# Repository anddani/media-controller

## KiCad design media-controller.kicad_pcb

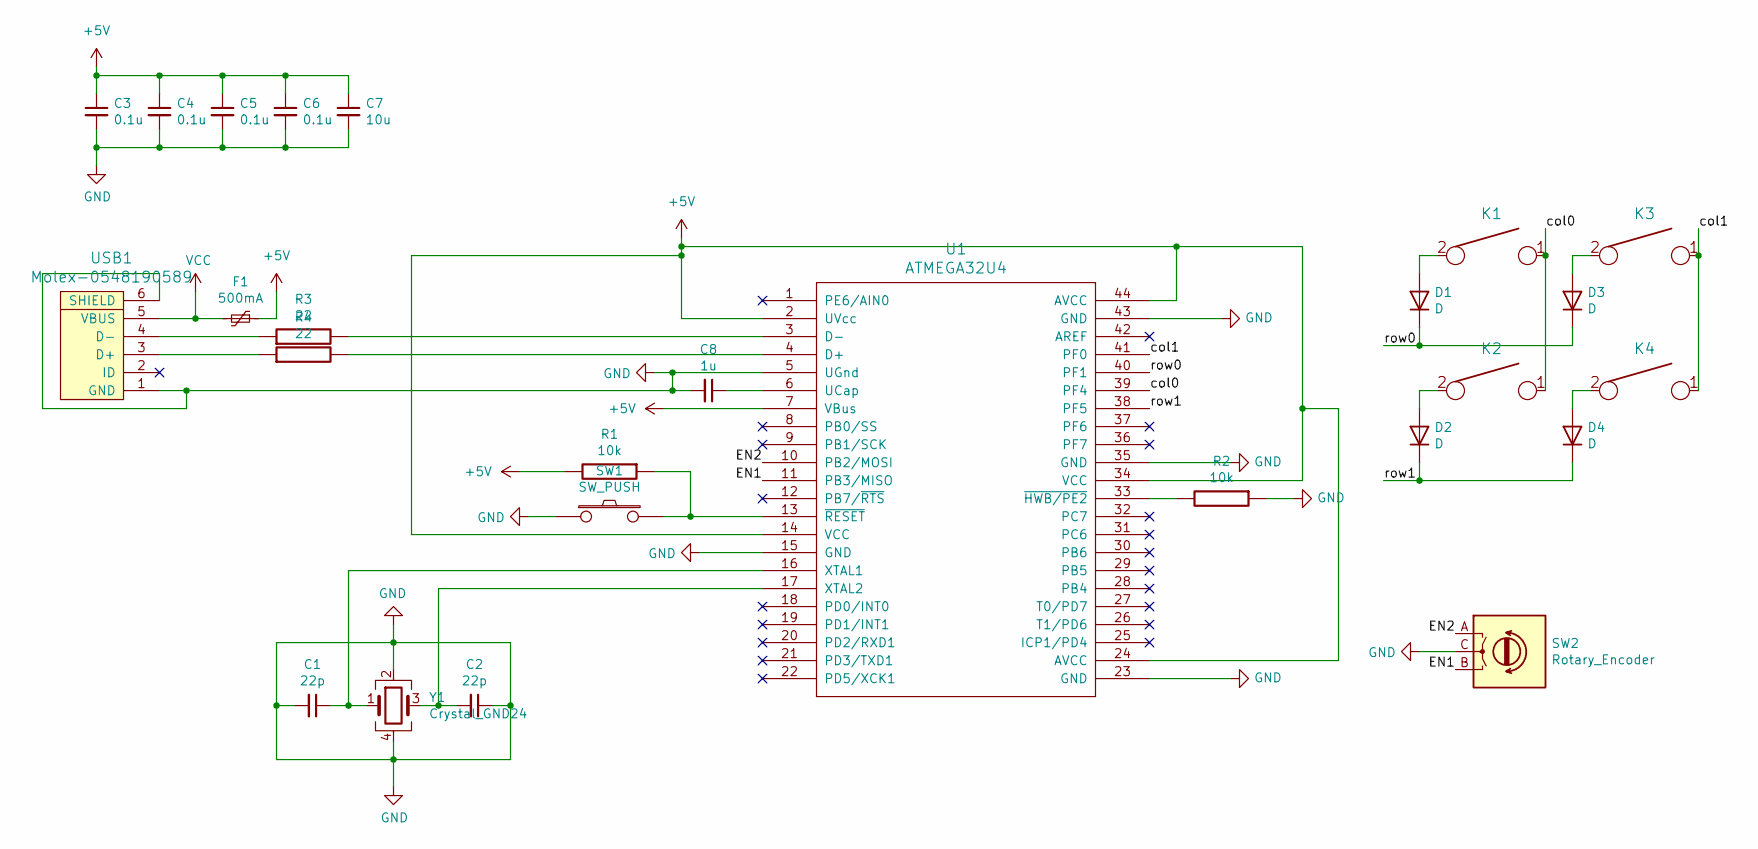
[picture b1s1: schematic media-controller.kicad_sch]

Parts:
C1, C2: 22p; C_0805_2012Metric
C3, C4, C5, C6: 0.1u; C_0805_2012Metric
C7: 10u; C_0805_2012Metric
C8: 1u; C_0805_2012Metric
D1, D2, D3, D4: D; D_SOD-123
F1: 500mA; Fuse_1206_3216Metric
K1, K2, K3, K4: KEYSW; MXOnly-1U-NoLED
R1, R2: 10k; R_0805_2012Metric
R3, R4: 22; R_0805_2012Metric
SW1: SW_PUSH; SKQG-1155865
SW2: Rotary_Encoder; RotaryEncoder_Alps_EC12E-Switch_Vertical_H20mm
U1: ATMEGA32U4; TQFP-44_10x10mm_P0.8mm
USB1: Molex-0548190589
Y1: Crystal_GND24; Crystal_SMD_3225-4Pin_3.2x2.5mm

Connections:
+5V: C3.1, C4.1, C5.1, C6.1, C7.1, F1.1, R1.2, U1.2 (UVcc), U1.7 (VBus), U1.14 (VCC), U1.24 (AVCC), U1.34 (VCC), U1.44 (AVCC)
/EN1: SW2.B, U1.11 (PB3/MISO)
/EN2: SW2.A, U1.10 (PB2/MOSI)
/col0: K1.1, K2.1, U1.39 (PF4)
/col1: K3.1, K4.1, U1.41 (PF0)
/row0: D1.1 (K), D3.1 (K), U1.40 (PF1)
/row1: D2.1 (K), D4.1 (K), U1.38 (PF5)
GND: C1.2, C2.1, C3.2, C4.2, C5.2, C6.2, C7.2, C8.2, R2.1, SW1.1, SW2.C, U1.5 (UGnd), U1.15 (GND), U1.23 (GND), U1.35 (GND), U1.43 (GND), USB1.1 (GND), USB1.6 (SHIELD), Y1.2, Y1.4
unnamed: C1.1, U1.16 (XTAL1), Y1.1
unnamed: C2.2, U1.17 (XTAL2), Y1.3
unnamed: C8.1, U1.6 (UCap)
unnamed: D1.2 (A), K1.2
unnamed: D2.2 (A), K2.2
unnamed: D3.2 (A), K3.2
unnamed: D4.2 (A), K4.2
unnamed: R1.1, SW1.2, U1.13 (~RESET)
unnamed: R2.2, U1.33 (~HWB/PE2)
unnamed: R3.1, USB1.4 (D-)
unnamed: R3.2, U1.3 (D-)
unnamed: R4.1, USB1.3 (D+)
unnamed: R4.2, U1.4 (D+)
VCC: F1.2, USB1.5 (VBUS)

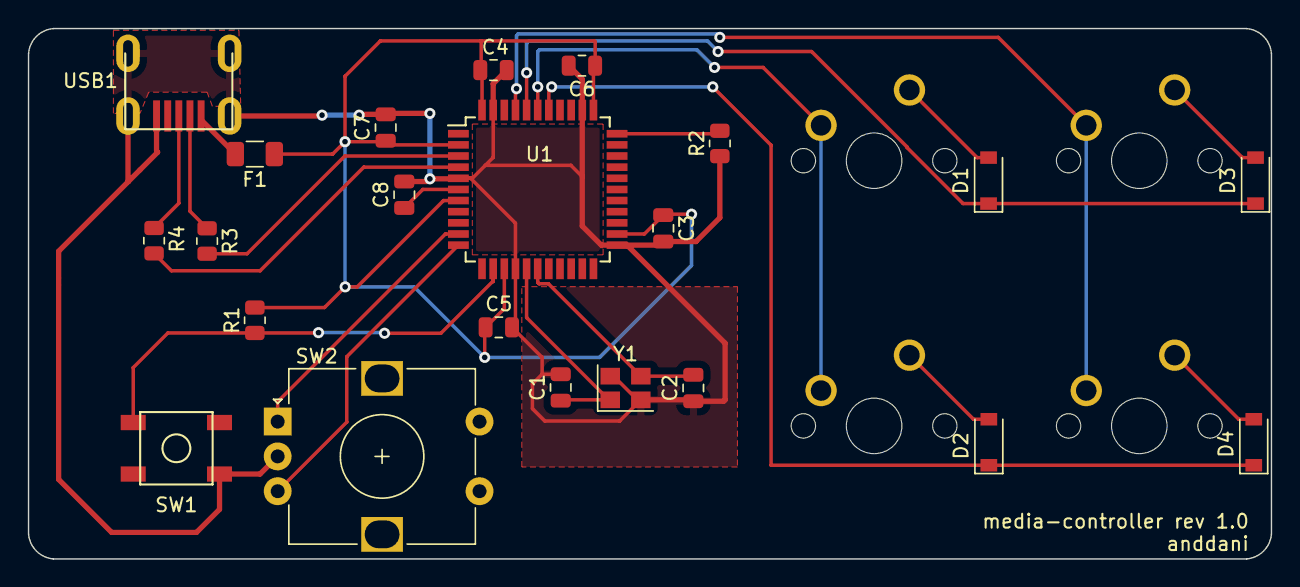
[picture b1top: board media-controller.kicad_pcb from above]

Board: 2 copper layers, 89.3 x 38.1 mm, 26 parts (0 on the bottom side), 22 nets.

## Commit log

2020-05-13 Add decoupling capacitors, usb port and reset switch
2020-05-13 Ignore cache and backup files
2020-08-18 Finish 2x2 media controller
2020-08-18 Use Device:Crystal_GND24 component
2020-08-18 Add rotary encoder
2022-04-29 Add kicad screenshot
2022-06-05 Finish routing
2022-06-05 Ignore gerber folder
2022-06-23 Add media controller render image
